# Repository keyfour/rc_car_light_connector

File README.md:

# RC Truck Light Connector

## Description

Addapter to connect extra lights for Tamiya RC Model truck.

There are two basic use cases:

1. Connect roof lights LEDs to single driver output (Lights extender)
2. Connect LEDs with different forward current rating (tested with 26mA and 33 mA LEDs)

## Board assembly and configuration

### BOM

| Part | Reference | Value | Use Case |
| ---- | --------- | ----- | -------- |
| Connectors | J1-J4 | B2B-PH-K-S(LF)(SN) | Any |
| Connectors | J5, J6 | B2B-PH-K-S(LF)(SN) | Lights extender |
| Resistors  | R1, R2 | 22 Ohm 0805 | Different LEDs |
| Resistors  | R1-R4  | 0 Ohm 0805  | Light extender |

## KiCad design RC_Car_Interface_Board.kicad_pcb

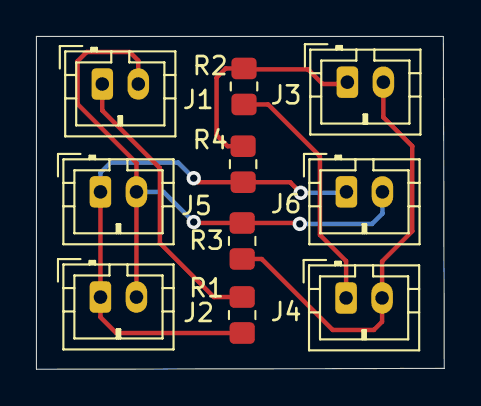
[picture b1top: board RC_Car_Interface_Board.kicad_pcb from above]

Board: 2 copper layers, 22.7 x 18.5 mm, 10 parts (0 on the bottom side), 6 nets.

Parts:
J1, J2, J3, J4, J5, J6: Conn_01x02; JST_PH_B2B-PH-K_1x02_P2.00mm_Vertical
R1, R2: 22; R_0805_2012Metric_Pad1.20x1.40mm_HandSolder
R3, R4: 0; R_0805_2012Metric_Pad1.20x1.40mm_HandSolder

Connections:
unnamed: J1.1, R1.2
unnamed: J1.2, J2.2, J5.2, J6.2, R3.2
unnamed: J2.1, J5.1, J6.1, R1.1, R4.2
unnamed: J3.1, R2.2, R4.1
unnamed: J3.2, J4.2, R3.1
unnamed: J4.1, R2.1

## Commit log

2021-05-16 Add README
